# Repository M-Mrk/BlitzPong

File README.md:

# BlitzPong

A precision trainer for table tennis that helps develop accuracy and ball placement control.

The device features 2 rows of 5 targets each. Targets illuminate to indicate where to hit, and your score increases with each successful hit.

**Note:** Current version supports individual row training without cross-row communication.
**Note:** Current hardware is wrong due to lcsc/Xinglight component change (see end). Do not try to build before this is addressed

## Use Case
Many table tennis players only focus on spin and speed, but neglect conscious placement to specific table zones. BlitzPong trains exactly that - precision targeting and shot placement.
Just place all the targets on the table, put the controller on the side, go through the setup and start the game.

## Why I made this
I noticed exactly what is mentioned above and was participating in [Hackclub's Blueprint](https://blueprint.hackclub.com) so I took the opportunity to build something for training precision or at least conscious.

# Pictures and Assembly
## Target
### PCB

- Place all components and solder
- Solder on piezo disc. Make sure to connect the bigger disc to the rounded pad
- Put isolating tape on the piezo disc on the side with the small disc
- Connect UPDI Serial tool and open [this](Software/target/platformio.ini) in PlatformIO and upload

### Case

- Print everything in PETG and the diffuser ring preferably in transparent PETG
- Push both bottom parts together
- Place all 8 LED pcbs and the target pcb
- Connect the LED pcbs with wires like [shown here](pictures/target-led-diagram.png)
- Solder wires to one female pogo connector and one male connector. (Watch out for the magnets!)
- Put pogo connectors into the cutouts and solder wires to target pcb ([diagram](pictures/target-pogo-diagram.png)). (Orient red mark of connector to where the M/F indent is and put female pogo connector in F cutout and vice versa)
- Slide both top parts together and press fit the diffuser
- Glue the piezo disc in the center of the bottom of the top parts
- Press top cover on and screw all 4 2.5x10mm screws in

## Controller
### PCB

**Note:** You may skip the eFuse and its passives. The picture also jumped (JP2) the eFuse, as it can be very hard to solder
- Place all SMD components and solder
- Print display adapter and place
- Place Display, Switches and Encoder and solder. Note that the encoder tabs might be very hard to solder as they are only designed to be wave soldered.
- Put on encoder cap and button caps

### Case

- Print everything
- Solder wires to male pogo connector and place connector in back piece (Put red marked side to where the M indent is)
- Place PCB in center part
- Feed wires through the back of pcb, trim and solder
- Screw on lid to back piece (2.5x10mm Screws)
- Connect MCU to computer, open [this](Software/controller/platformio.ini) in platformIO and upload 
- Press front cover on and screw all 3 pieces together with 2 screws on the side

# BOM
**Note:** The pogo connectors are from RTLECS with 6 Pins, Ears and straight pins
## Controller
|Reference   |Qty|Value                  |Datasheet                                                                                                                   |LCSC     |Link       |
|------------|---|-----------------------|----------------------------------------------------------------------------------------------------------------------------|---------|-----------|
|C1          |1  |22u                    |~                                                                                                                           |C309062  |           |
|C10         |1  |100n                   |~                                                                                                                           |C93194   |           |
|C11         |1  |10u                    |~                                                                                                                           |C3039694 |           |
|C12         |1  |22n                    |~                                                                                                                           |C1729    |           |
|C2,C3       |2  |4.7u                   |~                                                                                                                           |C51205   |           |
|C4,C5       |2  |10n                    |~                                                                                                                           |C83170   |           |
|C6          |1  |2.2n                   |~                                                                                                                           |C36576   |           |
|C7          |1  |22p                    |~                                                                                                                           |C2169931 |           |
|C8,C9       |2  |47u                    |~                                                                                                                           |C16780   |           |
|D1          |1  |SS54                   |~                                                                                                                           |C20609300|           |
|D2          |1  |LED                    |~                                                                                                                           |C51933292|           |
|D3          |1  |PWR_FLT                |~                                                                                                                           |C51933292|           |
|D4,D5       |2  |PRTR5V0U2X             |https://assets.nexperia.com/documents/data-sheet/PRTR5V0U2X.pdf                                                             |C5180302 |           |
|D6          |1  |~                      |https://item.szlcsc.com/datasheet/SMBJ24CA/975605.html                                                                      |C908853  |           |
|D7          |1  |~                      |https://www.ti.com/cn/lit/gpn/tpd4e05u06                                                                                    |C138714  |           |
|D8,D9       |2  |SMAJ6.0CA              |https://www.littelfuse.com/media?resourcetype=datasheets&itemid=75e32973-b177-4ee3-a0ff-cedaf1abdb93&filename=smaj-datasheet|C908810  |           |
|J2          |1  |Pogo_01x06_male        |~                                                                                                                           |         |https://aliexpress.com/item/1005005284441979.html|
|J3          |1  |G-Switch GT-USB-7010ASV|https://www.usb.org/sites/default/files/documents/usb_type-c.zip                                                            |C2988369 |           |
|J5          |1  |0.91 OLED              |~                                                                                                                           |C5248081 ||
|L1          |1  |4.7u                   |https://www.lcsc.com/datasheet/C5307631.pdf                                                                                 |C5307631 ||
|LCD1        |1  |2.42 OLED              |https://atta.szlcsc.com/upload/public/pdf/source/20230720/72FFD800C7ED95A3980F98F3DF4670E2.pdf                              |C7466001 ||
|Q1,Q2       |2  |BSS138                 |https://www.onsemi.com/pub/Collateral/BSS138-D.PDF                                                                          |C40912   ||
|R1          |1  |665k                   |~                                                                                                                           |C48533721||
|R10         |1  |37.4k                  |~                                                                                                                           |C2999586 ||
|R11         |1  |51.1                   |~                                                                                                                           |C2077153 ||
|R12         |1  |10.2k                  |~                                                                                                                           |C2933282 ||
|R13         |1  |1.96k                  |~                                                                                                                           |C2930163 ||
|R14,R18     |2  |120k                   |~                                                                                                                           |C17436   ||
|R15         |1  |6.49k                  |~                                                                                                                           |C2933484 ||
|R16         |1  |26.7k                  |~                                                                                                                           |C2999467 ||
|R17         |1  |20k                    |~                                                                                                                           |C2907240 ||
|R19         |1  |42.2k                  |~                                                                                                                           |C5119971 ||
|R2,R3,R4,R22|4  |4.7K                   |~                                                                                                                           |C2907499 ||
|R20         |1  |8.66k                  |~                                                                                                                           |C2933506 ||
|R21         |1  |150                    |~                                                                                                                           |C2907103 ||
|R5          |1  |24K                    |~                                                                                                                           |C2907246 ||
|R6          |1  |10                     |~                                                                                                                           |C17415   ||
|R7          |1  |10K                    |~                                                                                                                           |C84376   ||
|R8          |1  |68                     |~                                                                                                                           |C27592   ||
|R9          |1  |130k                   |~                                                                                                                           |C2933305 ||
|S1          |1  |PEC12R-4120F-S0012     |https://www.lcsc.com/datasheet/C143801.pdf                                                                                  |C143801  ||
|SW1,SW2,SW3 |3  |B3F-4055               |~                                                                                                                           |C36498965||
|U1          |1  |XIAO-ESP32-C6-SMD      |                                                                                                                            |         |https://aliexpress.com/item/1005010618607905.html|
|U2          |1  |CH224K                 |https://www.wch.cn/downloads/file/301.html                                                                                  |C970725  ||
|U3          |1  |TPS54531DDAR           |https://www.lcsc.com/datasheet/C50605.pdf                                                                                   |C50605   ||
|U4          |1  |AMS1117-3.3            |http://www.advanced-monolithic.com/pdf/ds1117.pdf                                                                           |C347222  ||
|U5          |1  |TPS25942ARVCR          |                                                                                                                            |C181295  ||
|            |4  |Screw 2,5x10mm         |~                                                                                                                           |         |https://www.ebay.de/itm/127200989742|

## Target (with LEDs)
|Reference   |Qty|Value                  |Datasheet                                                                                                                   |LCSC     |Link       |
|------------|---|-----------------------|----------------------------------------------------------------------------------------------------------------------------|---------|-----------|
|C1          |1  |100u                   |~                                                                                                                           |C15008   |           |
|C2,C3,C4,C5 |4  |100nC                  |~                                                                                                                           |C93194   |           |
|C6          |1  |10n                    |~                                                                                                                           |C83170   |           |
|D1          |1  |SS54                   |~                                                                                                                           |C20609300|           |
|D2,D3,D4,D5,D6,D7,D8,D9,D10,D11,D12,D13,D14,D15,D16,D17|16 |XL-5050RGBC-SK6812B    |https://cdn-shop.adafruit.com/product-files/1138/SK6812+LED+datasheet+.pdf       |C5349959 |           |
|D18,D21     |2  |PRTR5V0U2X             |https://assets.nexperia.com/documents/data-sheet/PRTR5V0U2X.pdf                                                             |C5180302 |           |
|D19,D22     |2  |SMAJ6.0CA              |https://www.littelfuse.com/media?resourcetype=datasheets&itemid=75e32973-b177-4ee3-a0ff-cedaf1abdb93&filename=smaj-datasheet|C908810  |           |
|D20         |1  |BAT54S                 |https://www.diodes.com/assets/Datasheets/ds11005.pdf                                                                        |C19726   |           |
|F1          |1  |Polyfuse IT2A          |~                                                                                                                           |C22366130|           |
|J1          |1  |Pogo_01x06_female      |~                                                                                                                           |         |https://aliexpress.com/item/1005005284441979.html|
|J2          |1  |Pogo_01x06_male        |~                                                                                                                           |         |https://aliexpress.com/item/1005005284441979.html|
|J5          |1  |Piezo                  |~                                                                                                                           |         |https://aliexpress.com/item/1005003133740770.html|
|Q1          |1  |SI2333CDS-HXY          |                                                                                                                            |C18198389|           |
|R1          |1  |47kR                   |~                                                                                                                           |C2907330 |           |
|R2,R3       |2  |10kR                   |~                                                                                                                           |C84376   |           |
|R4          |1  |1M                     |~                                                                                                                           |C17514   |           |
|U1          |1  |Attiny1614-SSF         |https://www.lcsc.com/datasheet/C614831.pdf                                                                                  |C614831  |           |
|            |4  |Screw 2,5x10mm         |~                                                                                                                           |         |https://www.ebay.de/itm/127200989742|

# Problems
I designed with 'XINGLIGHT XL-5050RGBC-SK6812B' LEDs in mind and they had the LCSC Number C5349959. I downloaded the datasheet, which you can view [here](misc/old-datasheet.pdf). As seen in the datasheet they work from 3.5 to 5.5 Volts and two of their pins are NC/Not connected. After ordering and soldering I couldn't get them to work reliably and so I redownloaded the datasheet. This [new datasheet](misc/new-datasheet.pdf) exclaims that they work with 9 to 14 Volt and all pins are populated and the order changed. What happend? When viewing the [JLCPCB component Library](https://jlcpcb.com/partdetail/XINGLIGHT-XL_5050RGBCSK6812B/C5349959) which only gets updated when the JLCPCB warehouse runs out of that part it still links the old datasheet and the same LCSC number C5349959. This means that between downloading the datasheet and ordering Xinglight replaced their XL-5050RGBC-SK6812B with a new model running at a completely different volatage and a different pin out, whilst keeping the same name and lcsc number. For now it is a miracle that they even work with just 5 Volt and light up with the wrong pinout, but they often don't turn off or correctly change color and are limited to single channel colors (so only red, green and blue).

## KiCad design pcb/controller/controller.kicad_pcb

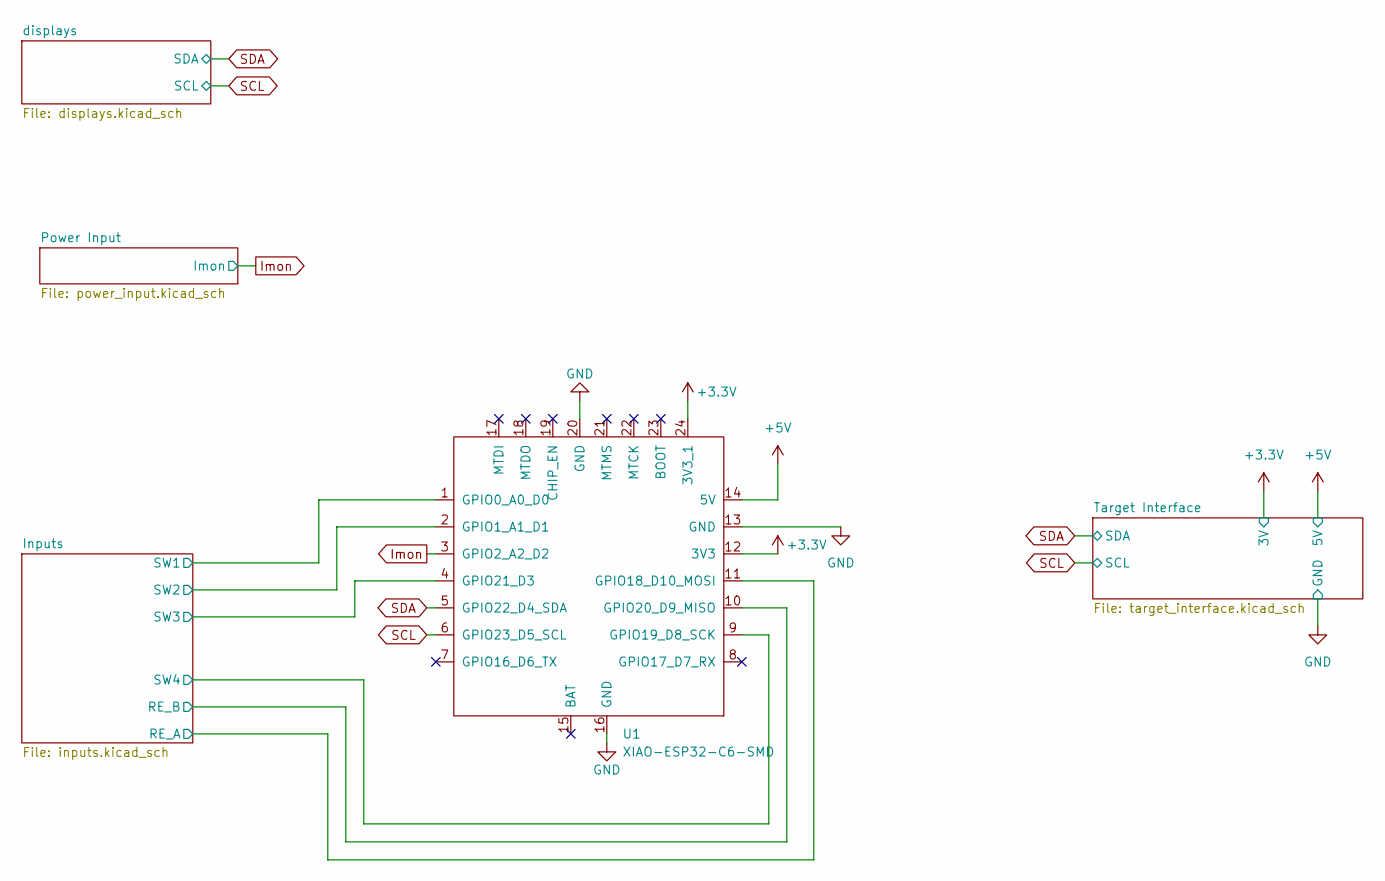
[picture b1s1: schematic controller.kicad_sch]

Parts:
U1: XIAO-ESP32-C6-SMD; XIAO-ESP32C6-SMD

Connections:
+3.3V: U1.12 (3V3), U1.24 (3V3_1); also elsewhere on the board
+5V: U1.14 (5V); also elsewhere on the board
/Inputs/RE_A: U1.11 (GPIO18_D10_MOSI); also elsewhere on the board
/Inputs/RE_B: U1.10 (GPIO20_D9_MISO); also elsewhere on the board
/Inputs/SW1: U1.1 (GPIO0_A0_D0); also elsewhere on the board
/Inputs/SW2: U1.2 (GPIO1_A1_D1); also elsewhere on the board
/Inputs/SW3: U1.4 (GPIO21_D3); also elsewhere on the board
/Inputs/SW4: U1.9 (GPIO19_D8_SCK); also elsewhere on the board
GND: U1.13 (GND), U1.16 (GND), U1.20 (GND); also elsewhere on the board
Imon: U1.3 (GPIO2_A2_D2); also elsewhere on the board
SCL: U1.6 (GPIO23_D5_SCL); also elsewhere on the board
SDA: U1.5 (GPIO22_D4_SDA); also elsewhere on the board

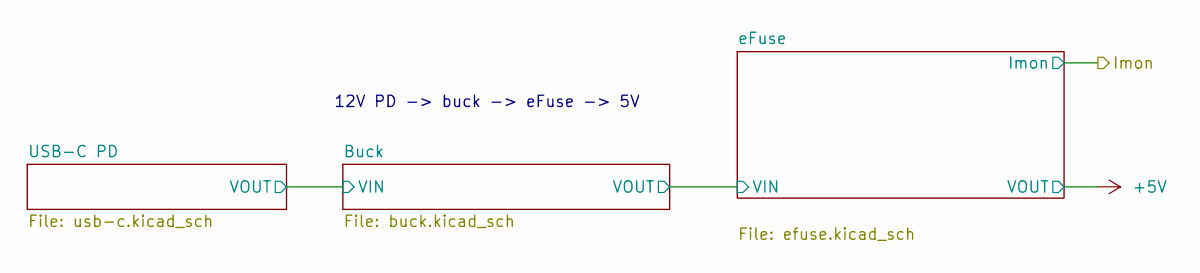
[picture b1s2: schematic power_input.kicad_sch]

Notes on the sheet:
12V PD -> buck -> eFuse -> 5V

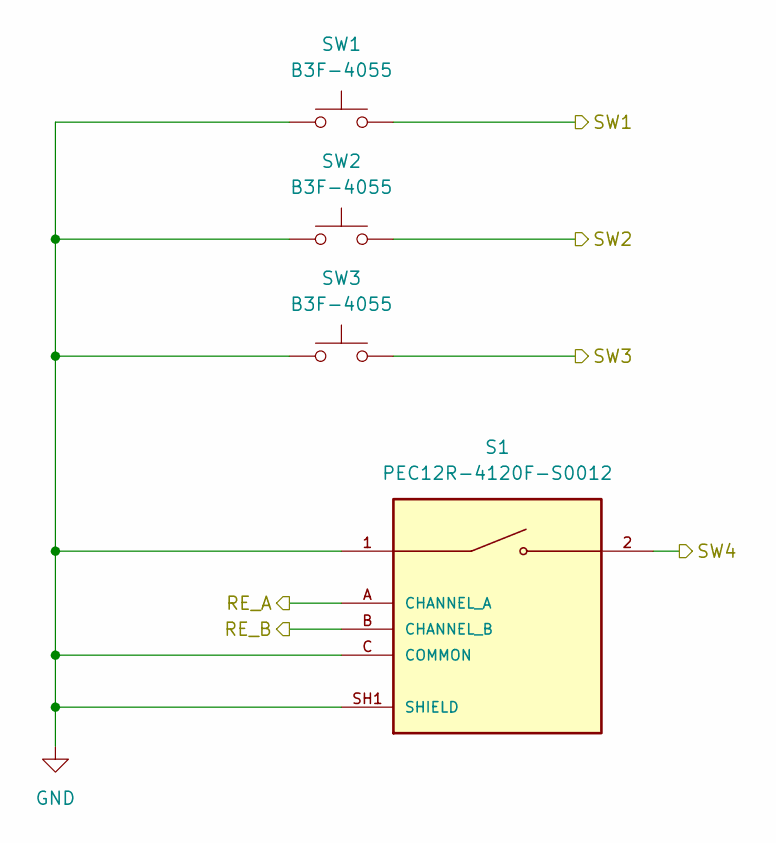
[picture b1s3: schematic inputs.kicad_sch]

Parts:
S1: PEC12R-4120F-S0012; XDCR_PEC12R-4120F-S0012; PARTREV 07/21; LCSC C143801
SW1, SW2, SW3: B3F-4055; SW_B3F-4055; LCSC C36498965

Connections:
/Inputs/RE_A: S1.A (CHANNEL_A); also elsewhere on the board
/Inputs/RE_B: S1.B (CHANNEL_B); also elsewhere on the board
/Inputs/SW1: SW1.2; also elsewhere on the board
/Inputs/SW2: SW2.2; also elsewhere on the board
/Inputs/SW3: SW3.2; also elsewhere on the board
/Inputs/SW4: S1.2; also elsewhere on the board
GND: S1.1, S1.C (COMMON), S1.SH1 (SHIELD), S1.SH2 (SHIELD), SW1.1, SW2.1, SW3.1; also elsewhere on the board

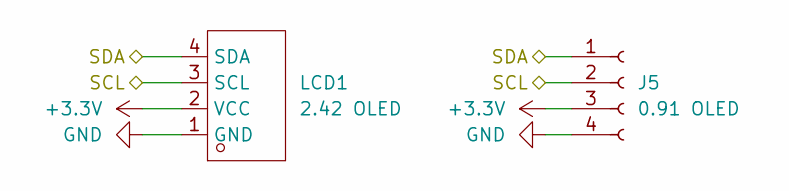
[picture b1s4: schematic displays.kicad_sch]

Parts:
J5: 0.91 OLED; SolderWire-0.5sqmm_1x04_P4.6mm_D0.9mm_OD2.1mm; LCSC C5248081
LCD1: 2.42 OLED; LCD-TH_4P-L72.0-W43.0-P2.54_HS242L03W2C01; Manufacturer Part HS242L03W2C01; LCSC Part Name 2.42'2.42寸 128*64 OLED显示屏 I2C通讯 SH1106 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

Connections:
+3.3V: J5.3, LCD1.2 (VCC); also elsewhere on the board
GND: J5.4, LCD1.1 (GND); also elsewhere on the board
SCL: J5.2, LCD1.3 (SCL); also elsewhere on the board
SDA: J5.1, LCD1.4 (SDA); also elsewhere on the board

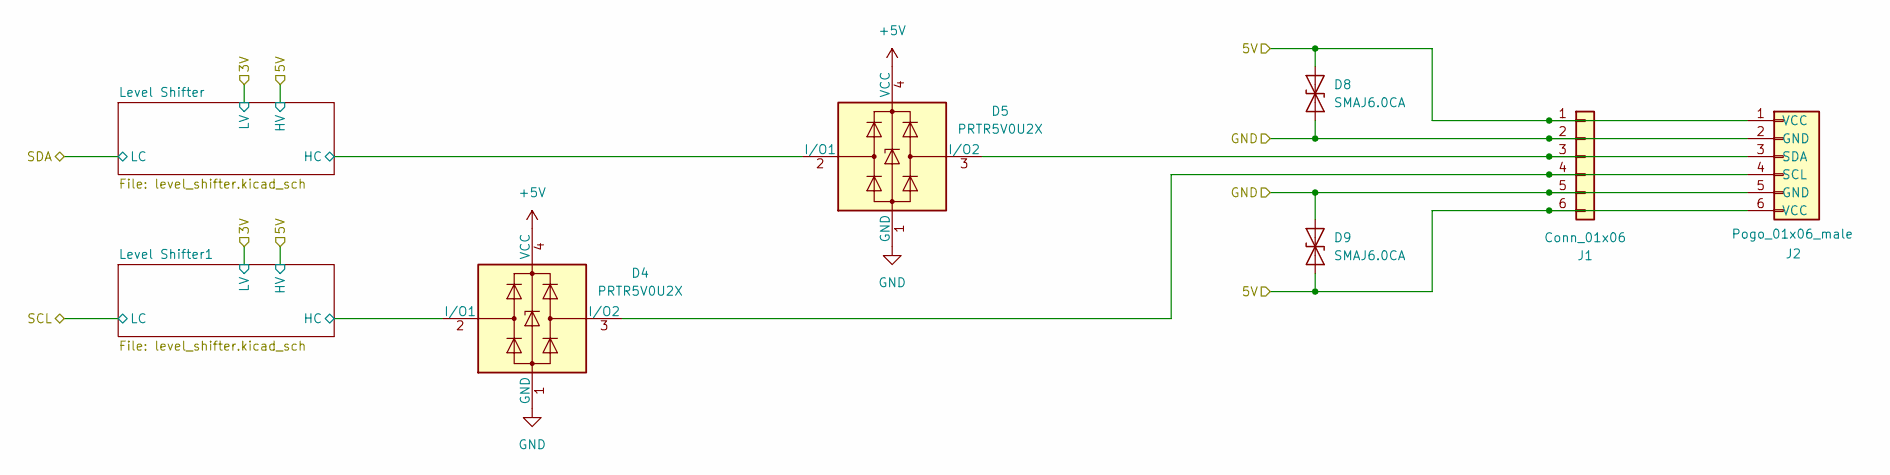
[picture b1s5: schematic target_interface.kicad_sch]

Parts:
D4, D5: PRTR5V0U2X; SOT-143; LCSC C5180302
D8, D9: SMAJ6.0CA; D_SMA; LCSC C908810
J1: Conn_01x06; SolderWire-1sqmm_1x06_P7.8mm_D1.4mm_OD3.9mm
J2: Pogo_01x06_male; 01x06 SMD 4x4mm pad

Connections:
+5V: D4.4 (VCC), D5.4 (VCC), D8.2 (A2), D9.1 (A1), J1.1, J1.6, J2.1 (VCC), J2.6 (VCC); also elsewhere on the board
/Target Interface/Level Shifter1/HC: D4.2 (I/O1); also elsewhere on the board
/Target Interface/Level Shifter/HC: D5.2 (I/O1); also elsewhere on the board
GND: D4.1 (GND), D5.1 (GND), D8.1 (A1), D9.2 (A2), J1.2, J1.5, J2.2 (GND), J2.5 (GND); also elsewhere on the board
unnamed: D4.3 (I/O2), J1.4, J2.4 (SCL)
unnamed: D5.3 (I/O2), J1.3, J2.3 (SDA)

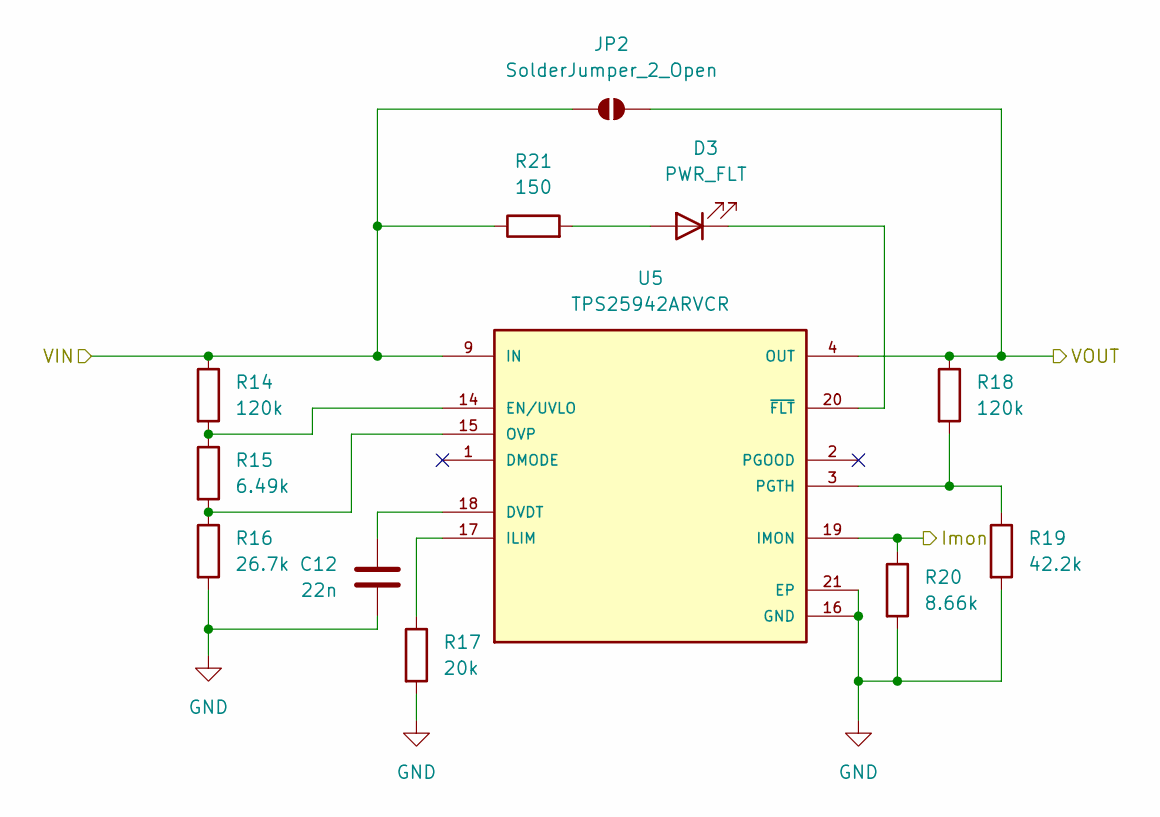
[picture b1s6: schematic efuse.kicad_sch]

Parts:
C12: 22n; C_0805_2012Metric; LCSC C1729
D3: PWR_FLT; LED_0603_1608Metric; LCSC C51933292
JP2: SolderJumper_2_Open; SolderJumper-2_P1.3mm_Open_Pad1.0x1.5mm
R14, R18: 120k; R_0805_2012Metric; LCSC C17436
R15: 6.49k; R_0805_2012Metric; LCSC C2933484
R16: 26.7k; R_0805_2012Metric; LCSC C2999467
R17: 20k; R_0805_2012Metric; LCSC C2907240
R19: 42.2k; R_0805_2012Metric; LCSC C5119971
R20: 8.66k; R_0805_2012Metric; LCSC C2933506
R21: 150; R_0603_1608Metric; LCSC C2907103
U5: TPS25942ARVCR; IC_TPS25942ARVCR; PARTREV D

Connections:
+5V: JP2.2 (B), R18.1, U5.4 (OUT), U5.5 (OUT), U5.6 (OUT), U5.7 (OUT), U5.8 (OUT); also elsewhere on the board
/Power Input/Buck/VOUT: JP2.1 (A), R14.1, R21.1, U5.9 (IN), U5.10 (IN), U5.11 (IN), U5.12 (IN), U5.13 (IN); also elsewhere on the board
GND: C12.2, R16.2, R17.2, R19.2, R20.2, U5.16 (GND), U5.21 (EP), U5.25; also elsewhere on the board
Imon: R20.1, U5.19 (IMON); also elsewhere on the board
unnamed 18: D3.2 (A), R21.2; also elsewhere on the board
unnamed 19: D3.1 (K), U5.20 (~FLT); also elsewhere on the board
unnamed: C12.1, U5.18 (DVDT)
unnamed: R14.2, R15.1, U5.14 (EN/UVLO)
unnamed: R17.1, U5.17 (ILIM)
unnamed: R15.2, R16.1, U5.15 (OVP)
unnamed: R18.2, R19.1, U5.3 (PGTH)

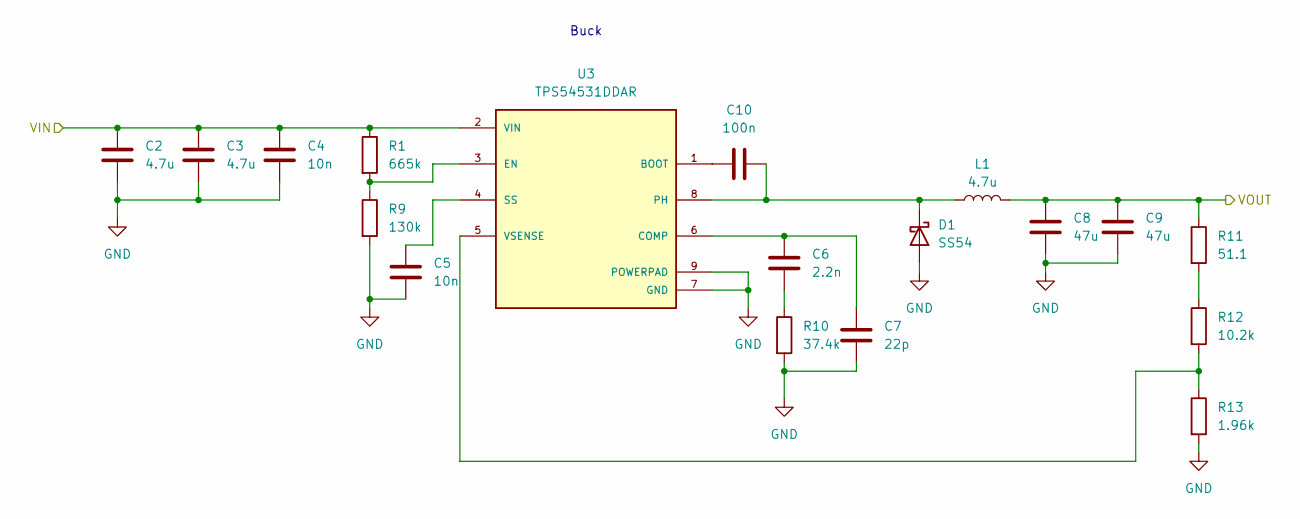
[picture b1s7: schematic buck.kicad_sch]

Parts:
C2, C3: 4.7u; C_1206_3216Metric; LCSC C51205
C4, C5: 10n; C_0805_2012Metric; LCSC C83170
C6: 2.2n; C_0805_2012Metric; LCSC C36576
C7: 22p; C_0603_1608Metric; LCSC C2169931
C8, C9: 47u; C_0805_2012Metric; LCSC C16780
C10: 100n; C_1206_3216Metric; LCSC C93194
D1: SS54; D_SMA; LCSC C20609300
L1: 4.7u; IND-SMD_L7.0-W6.6; LCSC C5307631
R1: 665k; R_0805_2012Metric; LCSC C48533721
R9: 130k; R_0805_2012Metric; LCSC C2933305
R10: 37.4k; R_0805_2012Metric; LCSC C2999586
R11: 51.1; R_0805_2012Metric; LCSC C2077153
R12: 10.2k; R_0805_2012Metric; LCSC C2933282
R13: 1.96k; R_0805_2012Metric; LCSC C2930163
U3: TPS54531DDAR; CONV_TPS54531DDAR; PARTREV A; LCSC C50605

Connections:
/Power Input/Buck/VIN: C2.1, C3.1, C4.1, R1.1, U3.2 (VIN); also elsewhere on the board
/Power Input/Buck/VOUT: C8.1, C9.1, L1.2, R11.1; also elsewhere on the board
GND: C2.2, C3.2, C4.2, C5.1, C7.2, C8.2, C9.2, D1.2 (A), R9.2, R10.2, R13.2, U3.7 (GND), U3.9 (POWERPAD), U3.10; also elsewhere on the board
unnamed: C6.2, R10.1
unnamed: C10.2, D1.1 (K), L1.1, U3.8 (PH)
unnamed: R11.2, R12.1
unnamed: C10.1, U3.1 (BOOT)
unnamed: C6.1, C7.1, U3.6 (COMP)
unnamed: R1.2, R9.1, U3.3 (EN)
unnamed: C5.2, U3.4 (SS)
unnamed: R12.2, R13.1, U3.5 (VSENSE)

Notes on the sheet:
Buck

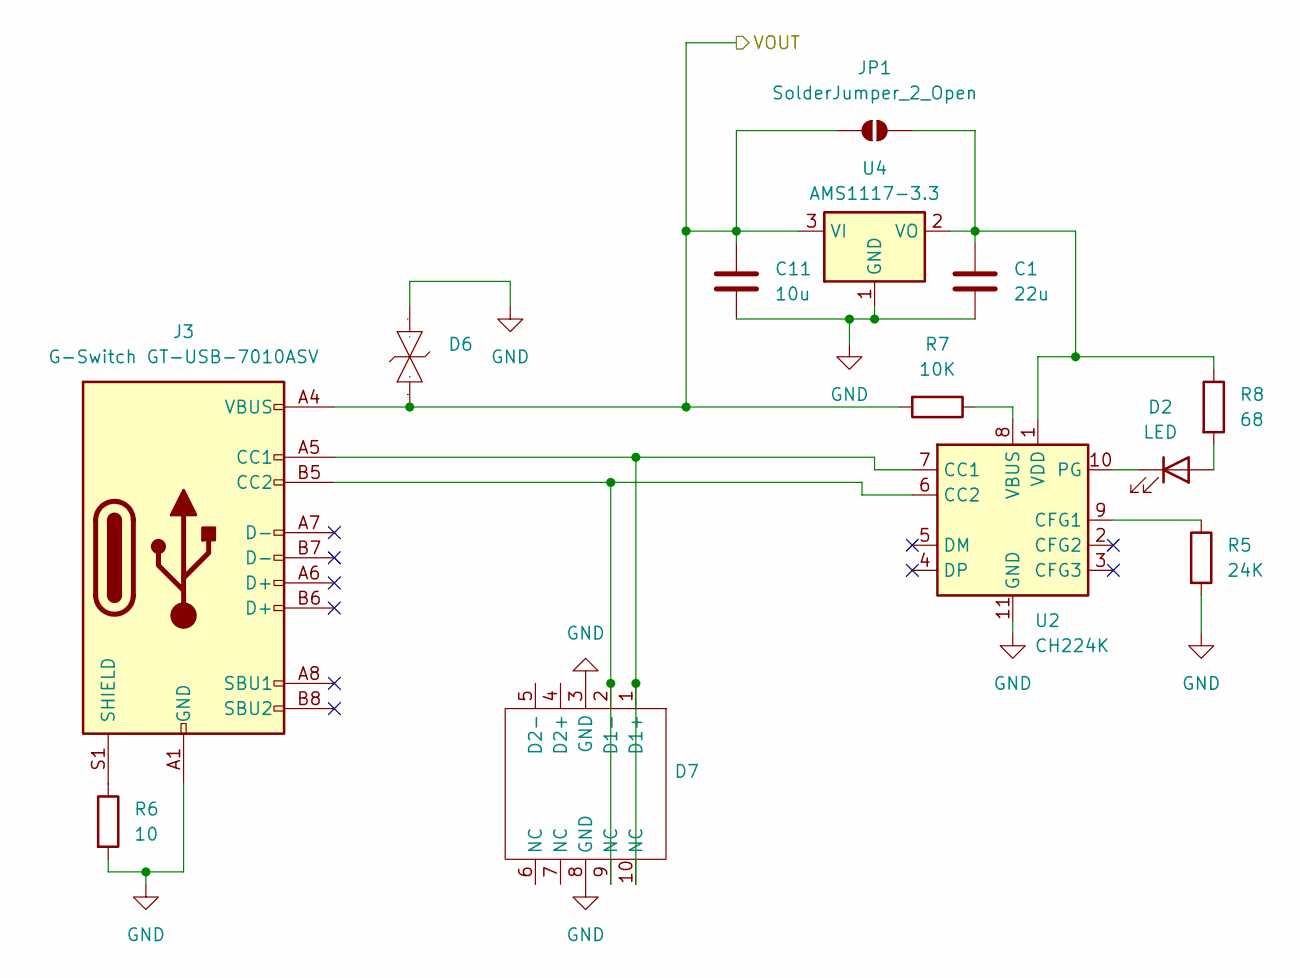
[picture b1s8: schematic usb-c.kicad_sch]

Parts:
C1: 22u; C_1210_3225Metric; LCSC C309062
C11: 10u; C_0805_2012Metric; LCSC C3039694
D2: LED; LED_0603_1608Metric; LCSC C51933292
D6: SMB_L4.4-W3.6-LS5.4-BI; Manufacturer Part SMBJ24CA; LCSC Part Name 双向TVS 24V截止 15.4A峰值脉冲
D7: USON-10_L2.5-W1.0-P0.50-BL; Manufacturer Part TPD4E05U06DQAR; LCSC Part Name 单向ESD
J3: G-Switch GT-USB-7010ASV; USB_C_Receptacle_G-Switch_GT-USB-7010ASV; LCSC C2988369
JP1: SolderJumper_2_Open; SolderJumper-2_P1.3mm_Open_TrianglePad1.0x1.5mm
R5: 24K; R_0805_2012Metric; LCSC C2907246
R6: 10; R_0805_2012Metric; LCSC C17415
R7: 10K; R_0805_2012Metric; LCSC C84376
R8: 68; R_0603_1608Metric; LCSC C27592
U2: CH224K; SSOP-10-1EP_3.9x4.9mm_P1mm_EP2.1x3.3mm_ThermalVias; LCSC C970725
U4: AMS1117-3.3; SOT-223-3_TabPin2; LCSC C347222

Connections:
/Power Input/Buck/VIN: C11.1, D6.1, J3.A4 (VBUS), J3.A9 (VBUS), J3.B4 (VBUS), J3.B9 (VBUS), JP1.2 (B), R7.2, U4.3 (VI); also elsewhere on the board
GND: C1.2, C11.2, D6.2, D7.3 (GND), D7.8 (GND), J3.A1 (GND), J3.A12 (GND), J3.B1 (GND), J3.B12 (GND), R5.2, R6.2, U2.11 (GND), U4.1 (GND); also elsewhere on the board
unnamed: D2.2 (A), R8.2
unnamed: D2.1 (K), U2.10 (PG)
unnamed: D7.1 (D1+), D7.10 (NC), J3.A5 (CC1), U2.7 (CC1)
unnamed: D7.2 (D1-), D7.9 (NC), J3.B5 (CC2), U2.6 (CC2)
unnamed: J3.S1 (SHIELD), R6.1
unnamed: C1.1, JP1.1 (A), R8.1, U2.1 (VDD), U4.2 (VO)
unnamed: R5.1, U2.9 (CFG1)
unnamed: R7.1, U2.8 (VBUS)

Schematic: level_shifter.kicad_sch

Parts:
Q1: BSS138; SOT-23; LCSC C40912
R2, R3: 4.7K; R_1206_3216Metric; LCSC C2907499

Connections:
+3.3V: Q1.1 (G), R2.1; also elsewhere on the board
+5V: R3.1; also elsewhere on the board
/Target Interface/Level Shifter/HC: Q1.3 (D), R3.2; also elsewhere on the board
SDA: Q1.2 (S), R2.2; also elsewhere on the board

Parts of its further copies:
Q2: BSS138; SOT-23; LCSC C40912
R4, R22: 4.7K; R_1206_3216Metric; LCSC C2907499

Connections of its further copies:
+3.3V: Q2.1 (G), R4.1; also elsewhere on the board
+5V: R22.1; also elsewhere on the board
/Target Interface/Level Shifter1/HC: Q2.3 (D), R22.2; also elsewhere on the board
SCL: Q2.2 (S), R4.2; also elsewhere on the board

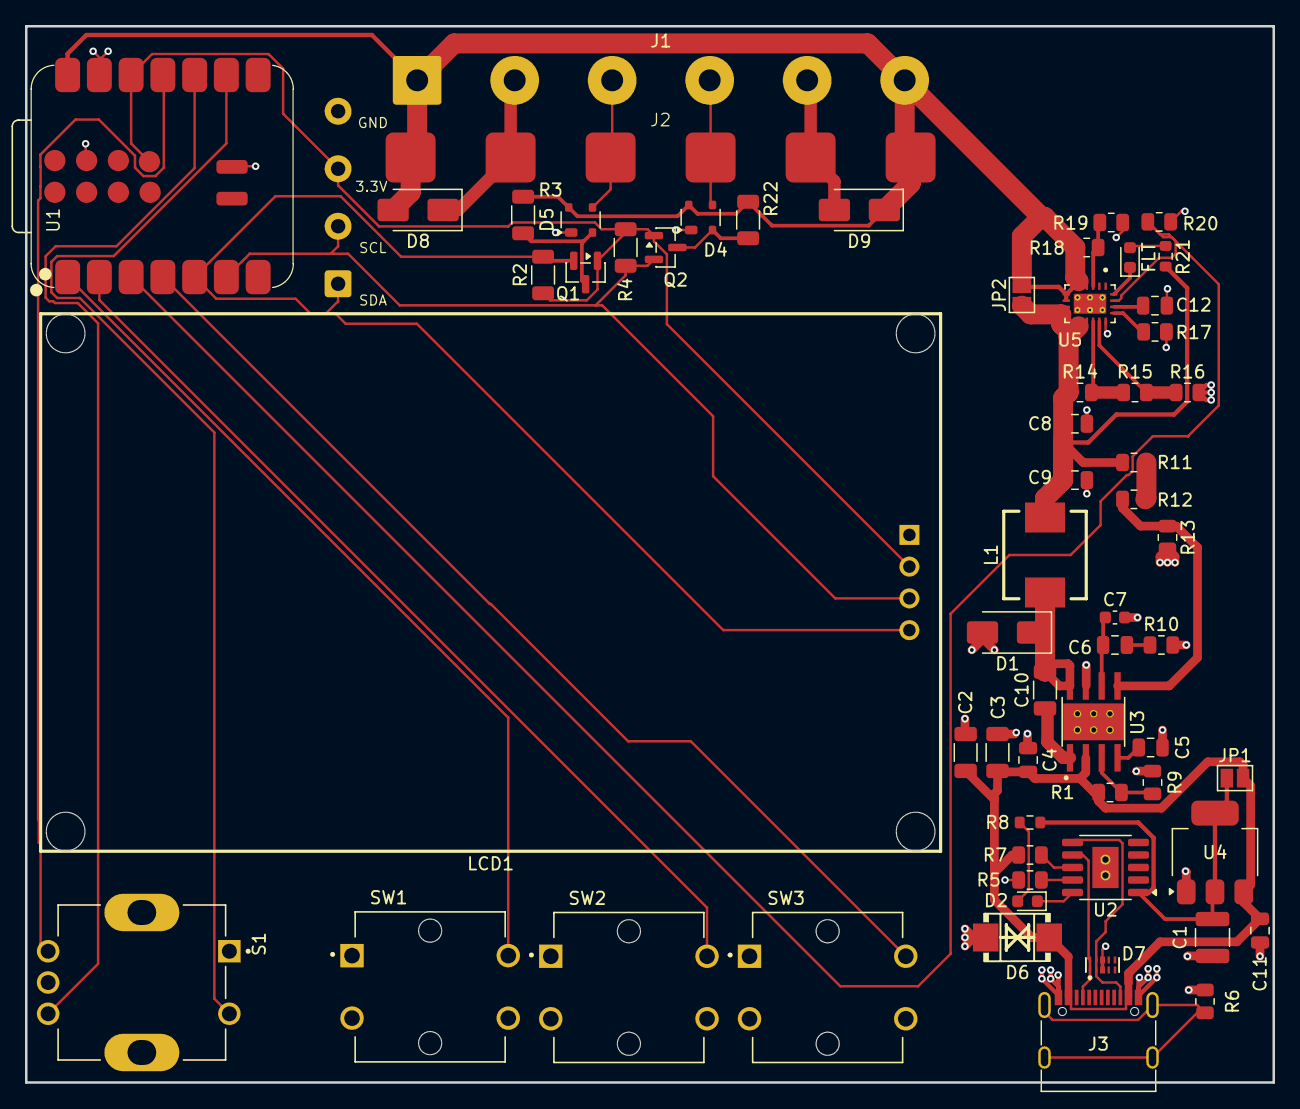
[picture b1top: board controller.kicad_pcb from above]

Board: 2 copper layers, 99.8 x 84.5 mm, 62 parts (1 on the bottom side), 41 nets.

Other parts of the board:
FLT: PWR_FLT; LED_0603_1608Metric

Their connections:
unnamed 18: FLT.2 (A); also elsewhere on the board
unnamed 19: FLT.1 (K); also elsewhere on the board

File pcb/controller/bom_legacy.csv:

"Source:","/home/matze/Projects/Hardware/PongTarget/pcb/controller/controller.kicad_sch"
"Date:","2025-12-06T14:23:39+0100"
"Tool:","Eeschema 9.0.5"
"Generator:","/usr/share/kicad/plugins/bom_csv_grouped_by_value_with_fp.py"
"Component Count:","53"
"Ref","Qnty","Value","Cmp name","Footprint","Description","Vendor","DNP"
"C1","1","22u","C","Capacitor_SMD:C_1206_3216Metric","Unpolarized capacitor","",""
"C2, C3","2","4.7u","C","Capacitor_SMD:C_1206_3216Metric","Unpolarized capacitor","",""
"C4, C5","2","10n","C","Capacitor_SMD:C_1206_3216Metric","Unpolarized capacitor","",""
"C6","1","2.2n","C","Capacitor_SMD:C_1206_3216Metric","Unpolarized capacitor","",""
"C7","1","22p","C","Capacitor_SMD:C_1206_3216Metric","Unpolarized capacitor","",""
"C8, C9","2","47u","C","Capacitor_SMD:C_1206_3216Metric","Unpolarized capacitor","",""
"C10","1","0.1u","C","Capacitor_SMD:C_1206_3216Metric","Unpolarized capacitor","",""
"C11","1","10u","C","Capacitor_SMD:C_1206_3216Metric","Unpolarized capacitor","",""
"C12","1","22n","C","Capacitor_SMD:C_1206_3216Metric","Unpolarized capacitor","",""
"D1","1","SS54","D_Schottky","","Schottky diode","",""
"D2","1","LED","LED","","Light emitting diode","",""
"D3","1","PWR_FLT","LED","","Light emitting diode","",""
"J1","1","Conn_01x06","Conn_01x06","Connector_Wire:SolderWire-1sqmm_1x06_P7.8mm_D1.4mm_OD3.9mm","Generic connector, single row, 01x06, script generated (kicad-library-utils/schlib/autogen/connector/)","",""
"J2","1","Pogo_01x06_male","Pogo_01x06_male","","Generic connector, single row, 01x06, script generated (kicad-library-utils/schlib/autogen/connector/)","",""
"J3","1","G-Switch GT-USB-7010ASV","USB_C_Receptacle_USB2.0_16P","Connector_USB:USB_C_Receptacle_G-Switch_GT-USB-7010ASV","USB 2.0-only 16P Type-C Receptacle connector","",""
"J4","1","2.4 OLED","Conn_01x04_Socket","","Generic connector, single row, 01x04, script generated","",""
"J5","1","0.96 OLED","Conn_01x04_Socket","","Generic connector, single row, 01x04, script generated","",""
"L1","1","4.7u","L","","Inductor","",""
"Q1, Q2","2","BSS138","BSS138","Package_TO_SOT_SMD:SOT-23","50V Vds, 0.22A Id, N-Channel MOSFET, SOT-23","",""
"R1","1","665k","R","Resistor_SMD:R_1206_3216Metric","Resistor","",""
"R2, R3, R4, R22","4","10k","R","Resistor_SMD:R_1206_3216Metric","Resistor","",""
"R5","1","24K","R","Resistor_SMD:R_1206_3216Metric","Resistor","",""
"R6","1","10","R","Resistor_SMD:R_1206_3216Metric","Resistor","",""
"R7","1","10K","R","Resistor_SMD:R_1206_3216Metric","Resistor","",""
"R8","1","150","R","Resistor_SMD:R_1206_3216Metric","Resistor","",""
"R9","1","130k","R","Resistor_SMD:R_1206_3216Metric","Resistor","",""
"R10","1","37.4k","R","Resistor_SMD:R_1206_3216Metric","Resistor","",""
"R11","1","51.1","R","Resistor_SMD:R_1206_3216Metric","Resistor","",""
"R12","1","10.2k","R","Resistor_SMD:R_1206_3216Metric","Resistor","",""
"R13","1","1.96k","R","Resistor_SMD:R_1206_3216Metric","Resistor","",""
"R14, R18","2","120k","R","Resistor_SMD:R_1206_3216Metric","Resistor","",""
"R15","1","6.49k","R","Resistor_SMD:R_1206_3216Metric","Resistor","",""
"R16","1","26.7k","R","Resistor_SMD:R_1206_3216Metric","Resistor","",""
"R17","1","20k","R","Resistor_SMD:R_1206_3216Metric","Resistor","",""
"R19","1","42.2k","R","Resistor_SMD:R_1206_3216Metric","Resistor","",""
"R20","1","8.66k","R","Resistor_SMD:R_1206_3216Metric","Resistor","",""
"R21","1","1.5k","R","Resistor_SMD:R_1206_3216Metric","Resistor","",""
"S1","1","PEC12R-4120F-S0012","PEC12R-4120F-S0012","PEC12R-4120F-S0012:XDCR_PEC12R-4120F-S0012","","",""
"SW1, SW2","2","B3F-4055","SW_Push","external_footprints.petty:SW_B3F-4055","Push button switch, generic, two pins","",""
"U1","1","XIAO-ESP32-C6-SMD","XIAO-ESP32-C6-SMD","","","",""
"U2","1","CH224K","CH224K","Package_SO:SSOP-10-1EP_3.9x4.9mm_P1mm_EP2.1x3.3mm_ThermalVias","100W USB Type-C PD3.0/2.0, BC1.2 Sink Controller, SSOP-10","",""
"U3","1","TPS54531DDAR","TPS54531DDAR","TPS54531DDAR:CONV_TPS54531DDAR","","",""
"U4","1","AMS1117-3.3","AMS1117-3.3","Package_TO_SOT_SMD:SOT-223-3_TabPin2","1A Low Dropout regulator, positive, 3.3V fixed output, SOT-223","",""
"U5","1","TPS25942ARVCR","TPS25942ARVCR","TPS25942ARVCR:IC_TPS25942ARVCR","","",""

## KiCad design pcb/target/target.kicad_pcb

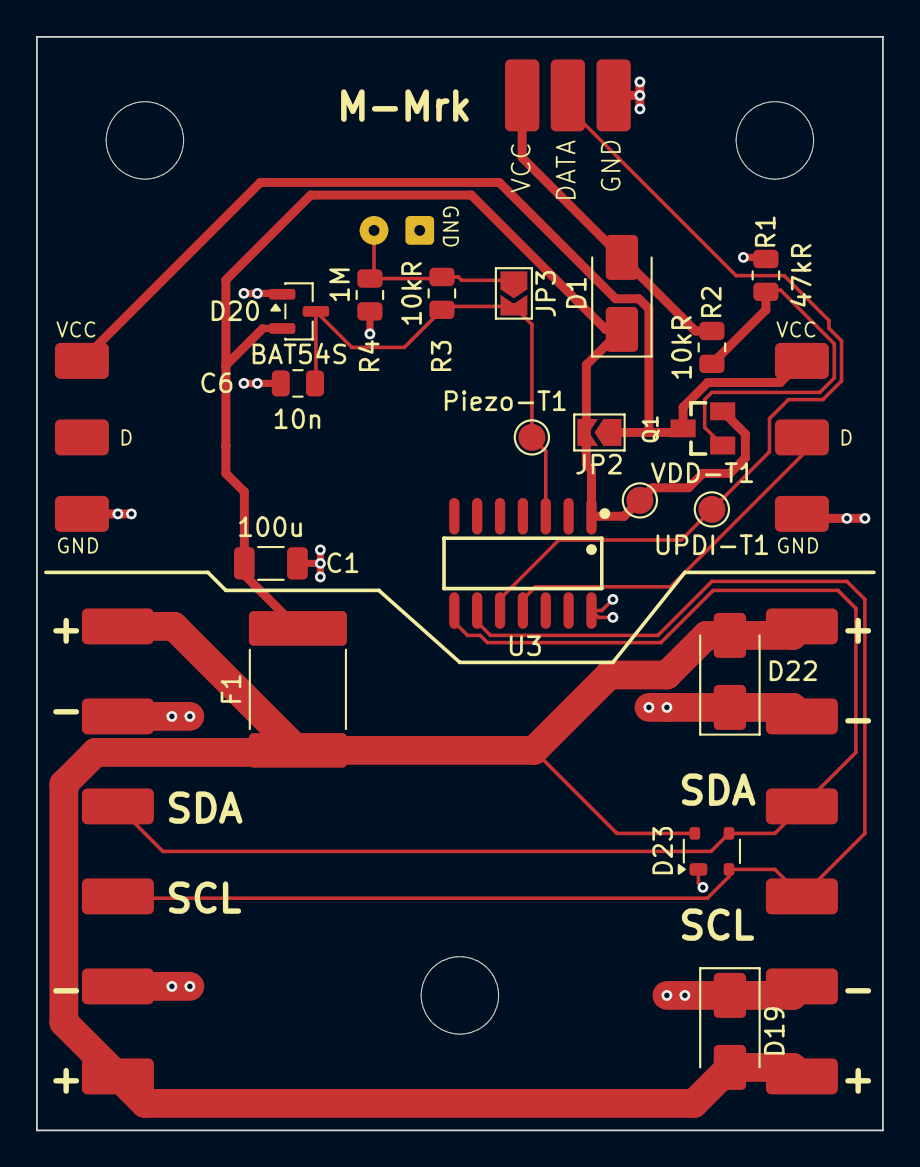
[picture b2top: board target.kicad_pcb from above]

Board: 2 copper layers, 47.0 x 60.8 mm, 25 parts (0 on the bottom side), 12 nets.

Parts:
C1: 100u; C_1206_3216Metric
C6: 10n; C_0805_2012Metric
D1: SS54; D_SMA
D19, D22: SMAJ6.0CA; D_SMA
D20: BAT54S; SOT-23
D23: PRTR5V0U2X; SOT-143
F1: Polyfuse IT2A; Fuse_2920_7451Metric
J1: Pogo_01x06_female; 01x06 SMD 4x4mm pad
J2: Pogo_01x06_male; 01x06 SMD 4x4mm pad
J3, J4: Conn_01x03_Pin; 01x03 SMD 2x3mm pad
J5: Piezo; SolderWire-0.1sqmm_1x02_P3.6mm_D0.4mm_OD1mm
JP2, JP3: SolderJumper_2_Open; SolderJumper-2_P1.3mm_Open_TrianglePad1.0x1.5mm
Piezo-T1: TestPoint; TestPoint_Pad_D1.5mm
Q1: SI2333CDS-HXY; SOT23
R1: 47kR; R_0805_2012Metric
R2, R3: 10kR; R_0805_2012Metric
R4: 1M; R_0805_2012Metric
U2: P2,54_MH3_pogo_updi
U3: SOIC-14_L8.7-W3.9-P1.27-LS6.0-BL
UPDI-T1: TestPoint; TestPoint_Pad_D1.5mm
VDD-T1: TestPoint; TestPoint_Pad_D1.5mm

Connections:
+5V: C1.1, D1.1 (K), D20.2 (K), F1.2, JP2.2 (B), Q1.2, U3.1 (VDD), VDD-T1.1
+5V Main: D19.2 (A2), D22.2 (A2), D23.4 (VCC), F1.1, J1.1 (VCC), J1.6 (VCC), J2.1 (VCC), J2.6 (VCC)
+5V UPDI: D1.2 (A), R2.1, U2.1 (VCC)
/LED Circle/VCC: J3.1, J4.1, JP2.1 (A), Q1.3
GND Main: C1.2, C6.2, D19.1 (A1), D20.1 (A), D22.1 (A1), D23.1 (GND), J1.2 (GND), J1.5 (GND), J2.2 (GND), J2.5 (GND), J3.3, J4.3, J5.1 (GND), R1.1, R4.2, U2.3 (GND), U3.14 (GND)
LED data: J3.2, U3.11 (PA1)
unnamed: J5.2 (OUT), JP3.1 (A), R3.1, R4.1
unnamed: Q1.1, R1.2, R2.2
Piezo: C6.1, D20.3 (COM), JP3.2 (B), Piezo-T1.1, R3.2, U3.3 (PA5)
SCL: D23.2 (I/O1), J1.4 (SCL), J2.4 (SCL), U3.9 (PB0)
SDA: D23.3 (I/O2), J1.3 (SDA), J2.3 (SDA), U3.8 (PB1)
UPDI pin: U2.2 (UPDI), U3.10 (PA0/RESET#/UPDI), UPDI-T1.1

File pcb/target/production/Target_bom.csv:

Designator,Footprint,Quantity,Value,LCSC Part #
C1,1206,1,100u,C15008
C6,0805,1,10n,C83170
D1,D_SMA,1,SS54,C20609300
"D19, D22",D_SMA,2,SMAJ6.0CA,C908810
D20,SOT-23,1,BAT54S,C19726
D23,SOT-143,1,PRTR5V0U2X,C5180302
F1,2920,1,Polyfuse IT2A,C22366130
"PIEZO-T1, UPDI-T1, VDD-T1",TestPoint_Pad_D1.5mm,3,TestPoint,
Q1,SOT23,1,SI2333CDS-HXY,C18198389
R1,0805,1,47kR,C2907330
"R2, R3",0805,2,10kR,C84376
R4,0805,1,1M,C17514
U3,SOIC-14_L8.7-W3.9-P1.27-LS6.0-BL,1,~,

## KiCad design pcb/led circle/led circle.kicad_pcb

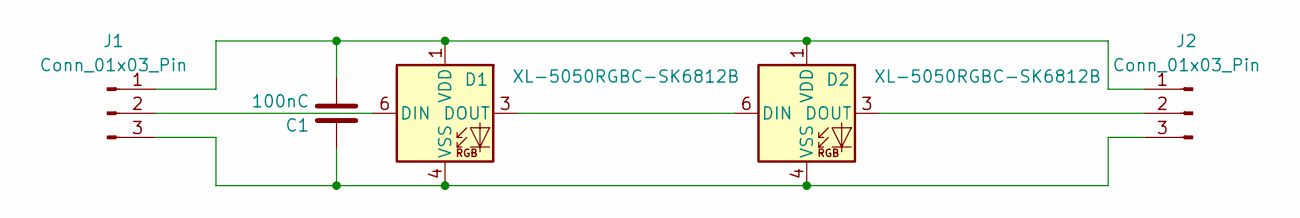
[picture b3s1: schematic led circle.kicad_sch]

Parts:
C1: 100nC; C_1206_3216Metric; LCSC C93194
D1, D2: XL-5050RGBC-SK6812B; LCSC C5349959
J1, J2: Conn_01x03_Pin; 01x03 SMD 2x3mm pad

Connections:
unnamed: D1.6 (DIN), J1.2
unnamed: D1.3 (DOUT), D2.6 (DIN)
unnamed: C1.2, D1.1 (VDD), D2.1 (VDD), J1.1, J2.1
unnamed: C1.1, D1.4 (VSS), D2.4 (VSS), J1.3, J2.3
unnamed: D2.3 (DOUT), J2.2

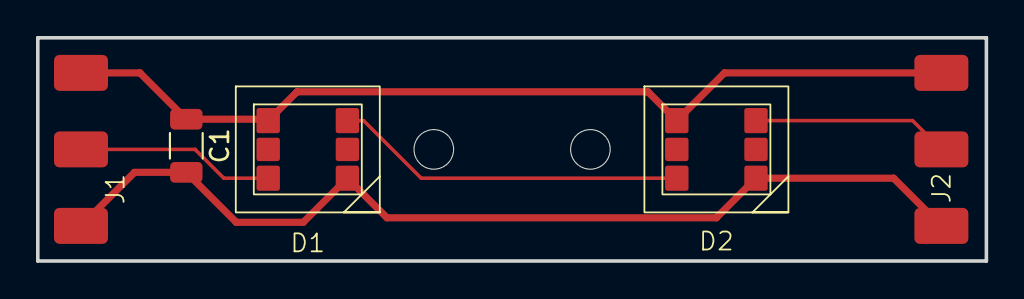
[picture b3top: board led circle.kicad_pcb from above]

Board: 2 copper layers, 52.7 x 12.4 mm, 5 parts (0 on the bottom side), 5 nets.
